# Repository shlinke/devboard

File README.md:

# devboard
A silly little DevBoard :3

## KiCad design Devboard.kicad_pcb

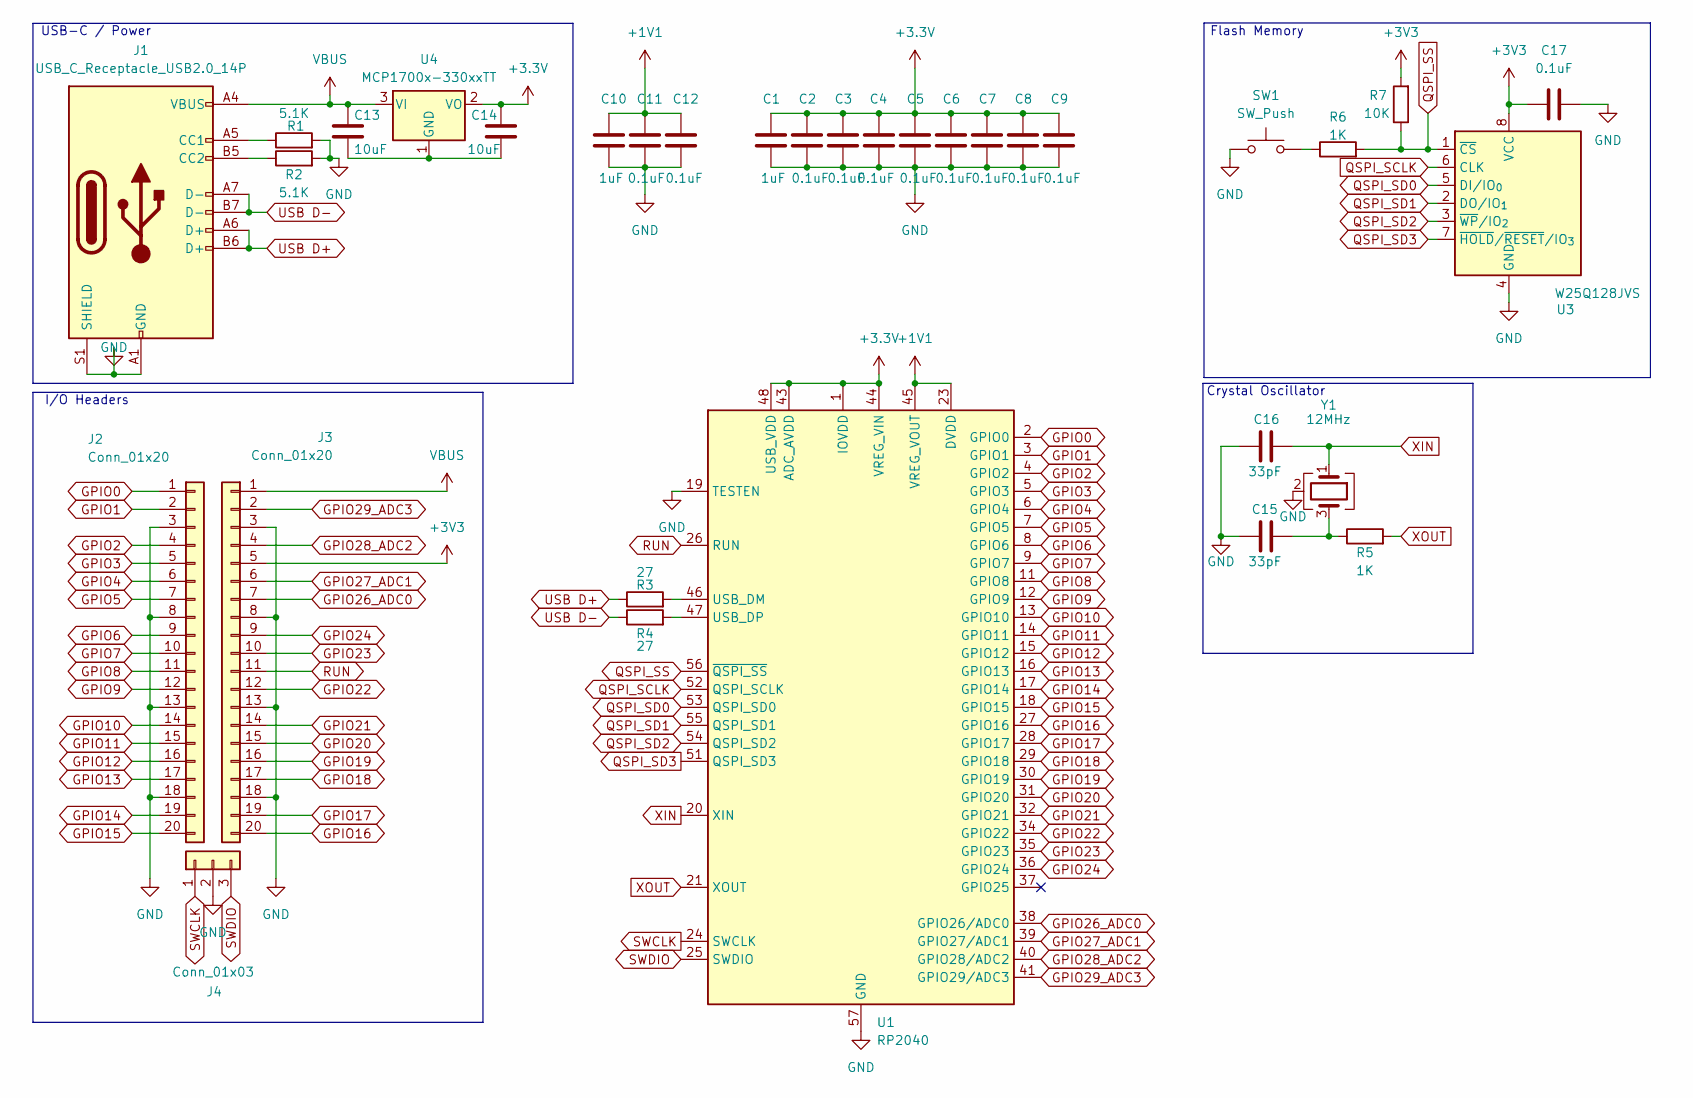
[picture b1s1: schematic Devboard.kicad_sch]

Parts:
C1, C10: 1uF; C_0402_1005Metric
C2, C3, C4, C5, C6, C7, C8, C9, C11, C12, C17: 0.1uF; C_0402_1005Metric
C13, C14: 10uF; C_0402_1005Metric
C15, C16: 33pF; C_0402_1005Metric
J1: USB_C_Receptacle_USB2.0_14P; USB_C_Receptacle_HRO_TYPE-C-31-M-12
J2, J3: Conn_01x20; PinHeader_1x20_P2.54mm_Vertical
J4: Conn_01x03; PinHeader_1x03_P2.54mm_Vertical
R1, R2: 5.1K; R_0402_1005Metric
R3, R4: 27; R_0402_1005Metric
R5, R6: 1K; R_0402_1005Metric
R7: 10K; R_0402_1005Metric
SW1: SW_Push; SW_Push_SPST_NO_Alps_SKRK
U1: RP2040; QFN-56-1EP_7x7mm_P0.4mm_EP3.2x3.2mm
U3: W25Q128JVS; Maxim_WSON-8-1EP_3x2mm_P0.5mm_EP1.75x1.63mm
U4: MCP1700x-330xxTT; SOT-23
Y1: 12MHz; Crystal_SMD_3225-4Pin_3.2x2.5mm

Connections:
+1V1: C10.1, C11.1, C12.1, U1.23 (DVDD), U1.45 (VREG_VOUT), U1.50 (DVDD)
+3.3V: C1.1, C2.1, C3.1, C4.1, C5.1, C6.1, C7.1, C8.1, C9.1, C14.1, U1.1 (IOVDD), U1.10 (IOVDD), U1.22 (IOVDD), U1.33 (IOVDD), U1.42 (IOVDD), U1.43 (ADC_AVDD), U1.44 (VREG_VIN), U1.48 (USB_VDD), U1.49 (IOVDD), U4.2 (VO)
+3V3: C17.1, J3.5, R7.2, U3.8 (VCC)
GND: C1.2, C2.2, C3.2, C4.2, C5.2, C6.2, C7.2, C8.2, C9.2, C10.2, C11.2, C12.2, C15.1, C16.1, C17.2, J1.A1 (GND), J1.A12 (GND), J1.B1 (GND), J1.B12 (GND), J1.S1 (SHIELD), J2.3, J2.8, J2.13, J2.18, J3.3, J3.8, J3.13, J3.18, J4.2, R1.2, R2.2, SW1.1, U1.19 (TESTEN), U1.57 (GND), U3.4 (GND), Y1.2 (G), Y1.4 (G)
GPIO0: J2.1, U1.2 (GPIO0)
GPIO1: J2.2, U1.3 (GPIO1)
GPIO2: J2.4, U1.4 (GPIO2)
GPIO3: J2.5, U1.5 (GPIO3)
GPIO4: J2.6, U1.6 (GPIO4)
GPIO5: J2.7, U1.7 (GPIO5)
GPIO6: J2.9, U1.8 (GPIO6)
GPIO7: J2.10, U1.9 (GPIO7)
GPIO8: J2.11, U1.11 (GPIO8)
GPIO9: J2.12, U1.12 (GPIO9)
GPIO10: J2.14, U1.13 (GPIO10)
GPIO11: J2.15, U1.14 (GPIO11)
GPIO12: J2.16, U1.15 (GPIO12)
GPIO13: J2.17, U1.16 (GPIO13)
GPIO14: J2.19, U1.17 (GPIO14)
GPIO15: J2.20, U1.18 (GPIO15)
GPIO16: J3.20, U1.27 (GPIO16)
GPIO17: J3.19, U1.28 (GPIO17)
GPIO18: J3.17, U1.29 (GPIO18)
GPIO19: J3.16, U1.30 (GPIO19)
GPIO20: J3.15, U1.31 (GPIO20)
GPIO21: J3.14, U1.32 (GPIO21)
GPIO22: J3.12, U1.34 (GPIO22)
GPIO23: J3.10, U1.35 (GPIO23)
GPIO24: J3.9, U1.36 (GPIO24)
GPIO26_ADC0: J3.7, U1.38 (GPIO26/ADC0)
GPIO27_ADC1: J3.6, U1.39 (GPIO27/ADC1)
GPIO28_ADC2: J3.4, U1.40 (GPIO28/ADC2)
GPIO29_ADC3: J3.2, U1.41 (GPIO29/ADC3)
unnamed: C15.2, R5.1, Y1.3
unnamed: J1.A5 (CC1), R1.1
unnamed: J1.B5 (CC2), R2.1
unnamed: R6.1, SW1.2
unnamed: R3.2, U1.46 (USB_DM)
unnamed: R4.2, U1.47 (USB_DP)
unnamed: C13.2, C14.2, U4.1 (GND)
QSPI_SCLK: U1.52 (QSPI_SCLK), U3.6 (CLK)
QSPI_SD0: U1.53 (QSPI_SD0), U3.5 (DI/IO_{0})
QSPI_SD1: U1.55 (QSPI_SD1), U3.2 (DO/IO_{1})
QSPI_SD2: U1.54 (QSPI_SD2), U3.3 (~WP/IO_{2})
QSPI_SD3: U1.51 (QSPI_SD3), U3.7 (~HOLD/~RESET/IO_{3})
QSPI_SS: R6.2, R7.1, U1.56 (~QSPI_SS), U3.1 (~CS)
RUN: J3.11, U1.26 (RUN)
SWCLK: J4.1, U1.24 (SWCLK)
SWDIO: J4.3, U1.25 (SWDIO)
USB D+: J1.A6 (D+), J1.B6 (D+), R3.1
USB D-: J1.A7 (D-), J1.B7 (D-), R4.1
VBUS: C13.1, J1.A4 (VBUS), J1.A9 (VBUS), J1.B4 (VBUS), J1.B9 (VBUS), J3.1, U4.3 (VI)
XIN: C16.2, U1.20 (XIN), Y1.1
XOUT: R5.2, U1.21 (XOUT)

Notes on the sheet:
Flash Memory
Crystal Oscillator
I/O Headers
USB-C / Power

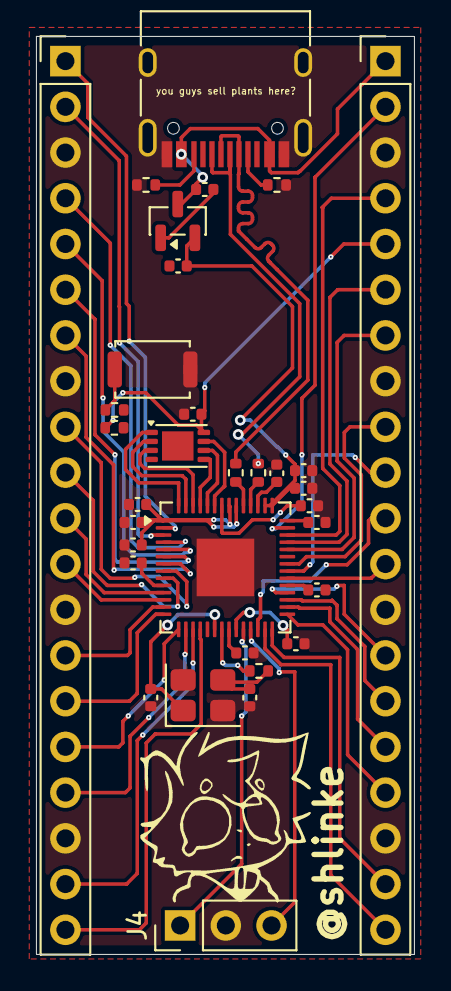
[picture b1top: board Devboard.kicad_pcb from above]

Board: 2 copper layers, 21.0 x 51.0 mm, 33 parts (0 on the bottom side), 54 nets.

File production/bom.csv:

Designator,Footprint,Quantity,Value,LCSC Part #
"C1, C10",0402,2,1uF,
"C11, C12, C17, C2, C3, C4, C5, C6, C7, C8, C9",0402,11,0.1uF,
"C13, C14",0402,2,10uF,
"C15, C16",0402,2,33pF,
J1,USB_C_Receptacle_HRO_TYPE-C-31-M-12,1,USB_C_Receptacle_USB2.0_14P,
"J2, J3",PinHeader_1x20_P2.54mm_Vertical,2,Conn_01x20,
J4,PinHeader_1x03_P2.54mm_Vertical,1,Conn_01x03,
"R1, R2",0402,2,5.1K,
"R3, R4",0402,2,27,
"R5, R6",0402,2,1K,
R7,0402,1,10K,
SW1,SW_Push_SPST_NO_Alps_SKRK,1,SW_Push,
U1,QFN-56-1EP_7x7mm_P0.4mm_EP3.2x3.2mm,1,RP2040,
U3,Maxim_WSON-8-1EP_3x2mm_P0.5mm_EP1.75x1.63mm,1,W25Q128JVS,
U4,SOT-23,1,MCP1700x-330xxTT,
Y1,Crystal_SMD_3225-4Pin_3.2x2.5mm,1,12MHz,

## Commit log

2026-03-22 Upload KiCAD and Production Files
